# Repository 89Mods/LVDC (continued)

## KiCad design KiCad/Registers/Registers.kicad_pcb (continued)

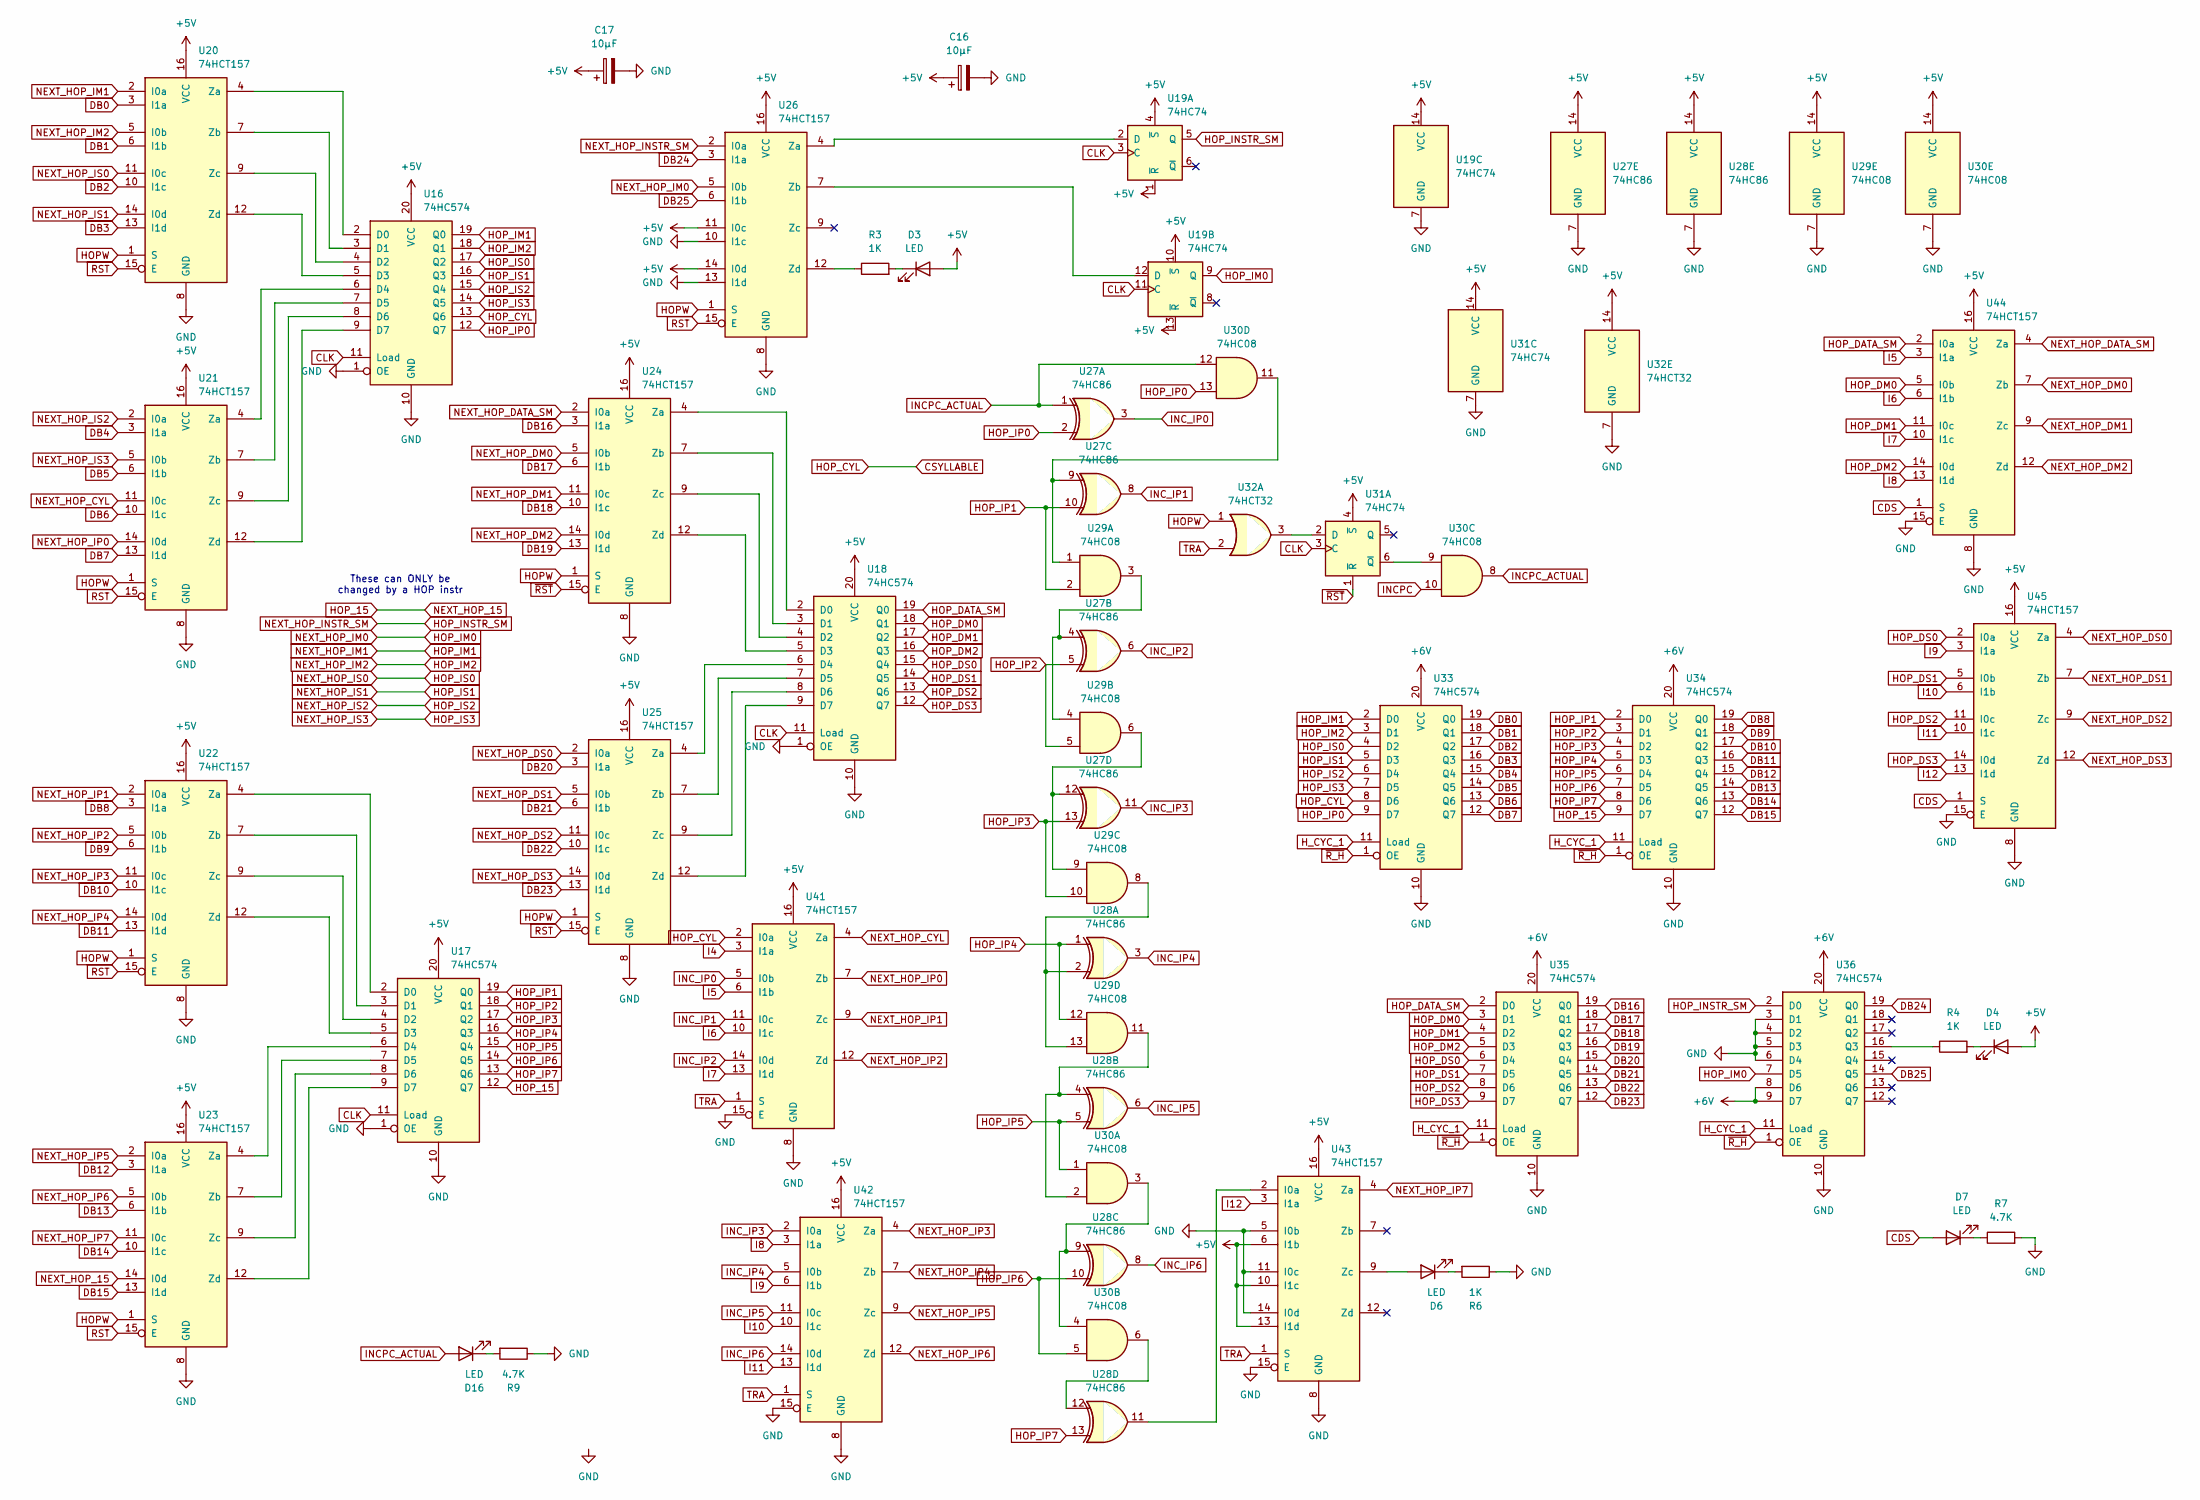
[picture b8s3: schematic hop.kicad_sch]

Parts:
C16, C17: 10µF; CP_Radial_D4.0mm_P2.00mm
D3, D4, D6, D7, D16: LED; LED_1206_3216Metric_Pad1.42x1.75mm_HandSolder
R3, R4, R6: 1K; R_1206_3216Metric_Pad1.30x1.75mm_HandSolder
R7, R9: 4.7K; R_1206_3216Metric_Pad1.30x1.75mm_HandSolder
U16, U17, U18, U33, U34, U35, U36: 74HC574; SO-20_12.8x7.5mm_P1.27mm
U19, U31: 74HC74; SO-14_3.9x8.65mm_P1.27mm
U20, U21, U22, U23, U24, U25, U26, U41, U42, U43, U44, U45: 74HCT157; SO-16_3.9x9.9mm_P1.27mm
U27, U28: 74HC86; SO-14_3.9x8.65mm_P1.27mm
U29, U30: 74HC08; SO-14_3.9x8.65mm_P1.27mm
U32: 74HCT32; SO-14_3.9x8.65mm_P1.27mm

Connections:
+5V: C16.1, C17.1, D3.2 (A), D4.2 (A), U16.20 (VCC), U17.20 (VCC), U18.20 (VCC), U19.1 (~R), U19.4 (~S), U19.10 (~S), U19.13 (~R), U19.14 (VCC), U20.16 (VCC), U21.16 (VCC), U22.16 (VCC), U23.16 (VCC), U24.16 (VCC), U25.16 (VCC), U26.11 (I0c), U26.14 (I0d), U26.16 (VCC), U27.14 (VCC), U28.14 (VCC), U29.14 (VCC), U30.14 (VCC), U31.4 (~S), U31.14 (VCC), U32.14 (VCC), U41.16 (VCC), U42.16 (VCC), U43.6 (I1b), U43.10 (I1c), U43.13 (I1d), U43.16 (VCC), U44.16 (VCC), U45.16 (VCC); also elsewhere on the board
+6V: U33.20 (VCC), U34.20 (VCC), U35.20 (VCC), U36.8 (D6), U36.9 (D7), U36.20 (VCC); also elsewhere on the board
CDS: D7.2 (A), U44.1 (S), U45.1 (S); also elsewhere on the board
CLK: U16.11 (Load), U17.11 (Load), U18.11 (Load), U19.3 (C), U19.11 (C), U31.3 (C); also elsewhere on the board
CSYLLABLE: U16.13 (Q6), U33.8 (D6), U41.2 (I0a); also elsewhere on the board
DB0: U20.3 (I1a), U33.19 (Q0); also elsewhere on the board
DB1: U20.6 (I1b), U33.18 (Q1); also elsewhere on the board
DB2: U20.10 (I1c), U33.17 (Q2); also elsewhere on the board
DB3: U20.13 (I1d), U33.16 (Q3); also elsewhere on the board
DB4: U21.3 (I1a), U33.15 (Q4); also elsewhere on the board
DB5: U21.6 (I1b), U33.14 (Q5); also elsewhere on the board
DB6: U21.10 (I1c), U33.13 (Q6); also elsewhere on the board
DB7: U21.13 (I1d), U33.12 (Q7); also elsewhere on the board
DB8: U22.3 (I1a), U34.19 (Q0); also elsewhere on the board
DB9: U22.6 (I1b), U34.18 (Q1); also elsewhere on the board
DB10: U22.10 (I1c), U34.17 (Q2); also elsewhere on the board
DB11: U22.13 (I1d), U34.16 (Q3); also elsewhere on the board
DB12: U23.3 (I1a), U34.15 (Q4); also elsewhere on the board
DB13: U23.6 (I1b), U34.14 (Q5); also elsewhere on the board
DB14: U23.10 (I1c), U34.13 (Q6); also elsewhere on the board
DB15: U23.13 (I1d), U34.12 (Q7); also elsewhere on the board
DB16: U24.3 (I1a), U35.19 (Q0); also elsewhere on the board
DB17: U24.6 (I1b), U35.18 (Q1); also elsewhere on the board
DB18: U24.10 (I1c), U35.17 (Q2); also elsewhere on the board
DB19: U24.13 (I1d), U35.16 (Q3); also elsewhere on the board
DB20: U25.3 (I1a), U35.15 (Q4); also elsewhere on the board
DB21: U25.6 (I1b), U35.14 (Q5); also elsewhere on the board
DB22: U25.10 (I1c), U35.13 (Q6); also elsewhere on the board
DB23: U25.13 (I1d), U35.12 (Q7); also elsewhere on the board
DB24: U26.3 (I1a), U36.19 (Q0); also elsewhere on the board
DB25: U26.6 (I1b), U36.14 (Q5); also elsewhere on the board
GND: C16.2, C17.2, R6.1, R7.2, R9.1, U16.1 (OE), U16.10 (GND), U17.1 (OE), U17.10 (GND), U18.1 (OE), U18.10 (GND), U19.7 (GND), U20.8 (GND), U21.8 (GND), U22.8 (GND), U23.8 (GND), U24.8 (GND), U25.8 (GND), U26.8 (GND), U26.10 (I1c), U26.13 (I1d), U27.7 (GND), U28.7 (GND), U29.7 (GND), U30.7 (GND), U31.7 (GND), U32.7 (GND), U33.10 (GND), U34.10 (GND), U35.10 (GND), U36.3 (D1), U36.4 (D2), U36.5 (D3), U36.6 (D4), U36.10 (GND), U41.8 (GND), U41.15 (E), U42.8 (GND), U42.15 (E), U43.5 (I0b), U43.8 (GND), U43.11 (I0c), U43.14 (I0d), U43.15 (E), U44.8 (GND), U44.15 (E), U45.8 (GND), U45.15 (E); also elsewhere on the board
HOPW: U20.1 (S), U21.1 (S), U22.1 (S), U23.1 (S), U24.1 (S), U25.1 (S), U26.1 (S), U32.1; also elsewhere on the board
HOP_15: U17.12 (Q7), U23.14 (I0d), U34.9 (D7); also elsewhere on the board
HOP_DATA_SM: U18.19 (Q0), U35.2 (D0), U44.2 (I0a)
HOP_DM0: U18.18 (Q1), U35.3 (D1), U44.5 (I0b); also elsewhere on the board
HOP_DM1: U18.17 (Q2), U35.4 (D2), U44.11 (I0c); also elsewhere on the board
HOP_DM2: U18.16 (Q3), U35.5 (D3), U44.14 (I0d); also elsewhere on the board
HOP_DS0: U18.15 (Q4), U35.6 (D4), U45.2 (I0a); also elsewhere on the board
HOP_DS1: U18.14 (Q5), U35.7 (D5), U45.5 (I0b); also elsewhere on the board
HOP_DS2: U18.13 (Q6), U35.8 (D6), U45.11 (I0c); also elsewhere on the board
HOP_DS3: U18.12 (Q7), U35.9 (D7), U45.14 (I0d); also elsewhere on the board
HOP_IM0: U19.9 (Q), U26.5 (I0b), U36.7 (D5); also elsewhere on the board
HOP_IM1: U16.19 (Q0), U20.2 (I0a), U33.2 (D0); also elsewhere on the board
HOP_IM2: U16.18 (Q1), U20.5 (I0b), U33.3 (D1); also elsewhere on the board
HOP_INSTR_SM: U19.5 (Q), U26.2 (I0a), U36.2 (D0)
HOP_IP0: U16.12 (Q7), U27.2, U30.13, U33.9 (D7); also elsewhere on the board
HOP_IP1: U17.19 (Q0), U27.10, U29.2, U34.2 (D0); also elsewhere on the board
HOP_IP2: U17.18 (Q1), U27.5, U29.5, U34.3 (D1); also elsewhere on the board
HOP_IP3: U17.17 (Q2), U27.13, U29.10, U34.4 (D2); also elsewhere on the board
HOP_IP4: U17.16 (Q3), U28.1, U29.12, U34.5 (D3); also elsewhere on the board
HOP_IP5: U17.15 (Q4), U28.5, U30.1, U34.6 (D4); also elsewhere on the board
HOP_IP6: U17.14 (Q5), U28.10, U30.5, U34.7 (D5); also elsewhere on the board
HOP_IP7: U17.13 (Q6), U28.13, U34.8 (D6); also elsewhere on the board
HOP_IS0: U16.17 (Q2), U20.11 (I0c), U33.4 (D2); also elsewhere on the board
HOP_IS1: U16.16 (Q3), U20.14 (I0d), U33.5 (D3); also elsewhere on the board
HOP_IS2: U16.15 (Q4), U21.2 (I0a), U33.6 (D4); also elsewhere on the board
HOP_IS3: U16.14 (Q5), U21.5 (I0b), U33.7 (D5); also elsewhere on the board
H_CYC_1: U33.11 (Load), U34.11 (Load), U35.11 (Load), U36.11 (Load); also elsewhere on the board
I4: U41.3 (I1a); also elsewhere on the board
I5: U41.6 (I1b), U44.3 (I1a); also elsewhere on the board
I6: U41.10 (I1c), U44.6 (I1b); also elsewhere on the board
I7: U41.13 (I1d), U44.10 (I1c); also elsewhere on the board
I8: U42.3 (I1a), U44.13 (I1d); also elsewhere on the board
I9: U42.6 (I1b), U45.3 (I1a); also elsewhere on the board
I10: U42.10 (I1c), U45.6 (I1b); also elsewhere on the board
I11: U42.13 (I1d), U45.10 (I1c); also elsewhere on the board
I12: U43.3 (I1a), U45.13 (I1d); also elsewhere on the board
INCPC: U30.10; also elsewhere on the board
INCPC_ACTUAL: D16.2 (A), U27.1, U30.8, U30.12
INC_IP0: U27.3, U41.5 (I0b)
INC_IP1: U27.8, U41.11 (I0c)
INC_IP2: U27.6, U41.14 (I0d)
INC_IP3: U27.11, U42.2 (I0a)
INC_IP4: U28.3, U42.5 (I0b)
INC_IP5: U28.6, U42.11 (I0c)
INC_IP6: U28.8, U42.14 (I0d)
NEXT_HOP_CYL: U21.11 (I0c), U41.4 (Za)
NEXT_HOP_DATA_SM: U24.2 (I0a), U44.4 (Za)
NEXT_HOP_DM0: U24.5 (I0b), U44.7 (Zb)
NEXT_HOP_DM1: U24.11 (I0c), U44.9 (Zc)
NEXT_HOP_DM2: U24.14 (I0d), U44.12 (Zd)
NEXT_HOP_DS0: U25.2 (I0a), U45.4 (Za)
NEXT_HOP_DS1: U25.5 (I0b), U45.7 (Zb)
NEXT_HOP_DS2: U25.11 (I0c), U45.9 (Zc)
NEXT_HOP_DS3: U25.14 (I0d), U45.12 (Zd)
NEXT_HOP_IP0: U21.14 (I0d), U41.7 (Zb)
NEXT_HOP_IP1: U22.2 (I0a), U41.9 (Zc)
NEXT_HOP_IP2: U22.5 (I0b), U41.12 (Zd)
NEXT_HOP_IP3: U22.11 (I0c), U42.4 (Za)
NEXT_HOP_IP4: U22.14 (I0d), U42.7 (Zb)
NEXT_HOP_IP5: U23.2 (I0a), U42.9 (Zc)
NEXT_HOP_IP6: U23.5 (I0b), U42.12 (Zd)
NEXT_HOP_IP7: U23.11 (I0c), U43.4 (Za)
unnamed: D3.1 (K), R3.2
unnamed: D4.1 (K), R4.2
unnamed: D6.2 (A), U43.9 (Zc)
unnamed: D6.1 (K), R6.2
unnamed: D7.1 (K), R7.1
unnamed: D16.1 (K), R9.2
unnamed: U16.2 (D0), U20.4 (Za)
unnamed: U16.3 (D1), U20.7 (Zb)
unnamed: U16.4 (D2), U20.9 (Zc)
unnamed: U16.5 (D3), U20.12 (Zd)
unnamed: U16.6 (D4), U21.4 (Za)
unnamed: U16.7 (D5), U21.7 (Zb)
unnamed: U16.8 (D6), U21.9 (Zc)
unnamed: U16.9 (D7), U21.12 (Zd)
unnamed: U17.2 (D0), U22.4 (Za)
unnamed: U17.3 (D1), U22.7 (Zb)
unnamed: U17.4 (D2), U22.9 (Zc)
unnamed: U17.5 (D3), U22.12 (Zd)
unnamed: U17.6 (D4), U23.4 (Za)
unnamed: U17.7 (D5), U23.7 (Zb)
unnamed: U17.8 (D6), U23.9 (Zc)
unnamed: U17.9 (D7), U23.12 (Zd)
unnamed: U18.2 (D0), U24.4 (Za)
unnamed: U18.3 (D1), U24.7 (Zb)
unnamed: U18.4 (D2), U24.9 (Zc)
unnamed: U18.5 (D3), U24.12 (Zd)
unnamed: U18.6 (D4), U25.4 (Za)
unnamed: U18.7 (D5), U25.7 (Zb)
unnamed: U18.8 (D6), U25.9 (Zc)
unnamed: U18.9 (D7), U25.12 (Zd)
unnamed: U19.2 (D), U26.4 (Za)
unnamed: U19.12 (D), U26.7 (Zb)
unnamed: R3.1, U26.12 (Zd)
unnamed: U27.4, U29.3, U29.4
unnamed: U27.9, U29.1, U30.11
unnamed: U27.12, U29.6, U29.9
unnamed: U28.2, U29.8, U29.13
unnamed: U28.4, U29.11, U30.2
unnamed: U28.9, U30.3, U30.4
unnamed: U28.12, U30.6
unnamed: U31.2 (D), U32.3
unnamed: U30.9, U31.6 (~Q)
unnamed: R4.1, U36.16 (Q3)
unnamed: U28.11, U43.2 (I0a)
RST: U20.15 (E), U21.15 (E), U22.15 (E), U23.15 (E), U25.15 (E), U26.15 (E); also elsewhere on the board
TRA: U32.2, U41.1 (S), U42.1 (S), U43.1 (S); also elsewhere on the board
~RST: U24.15 (E), U31.1 (~R); also elsewhere on the board
~R_H: U33.1 (OE), U34.1 (OE), U35.1 (OE), U36.1 (OE); also elsewhere on the board

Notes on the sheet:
These can ONLY be changed by a HOP instr

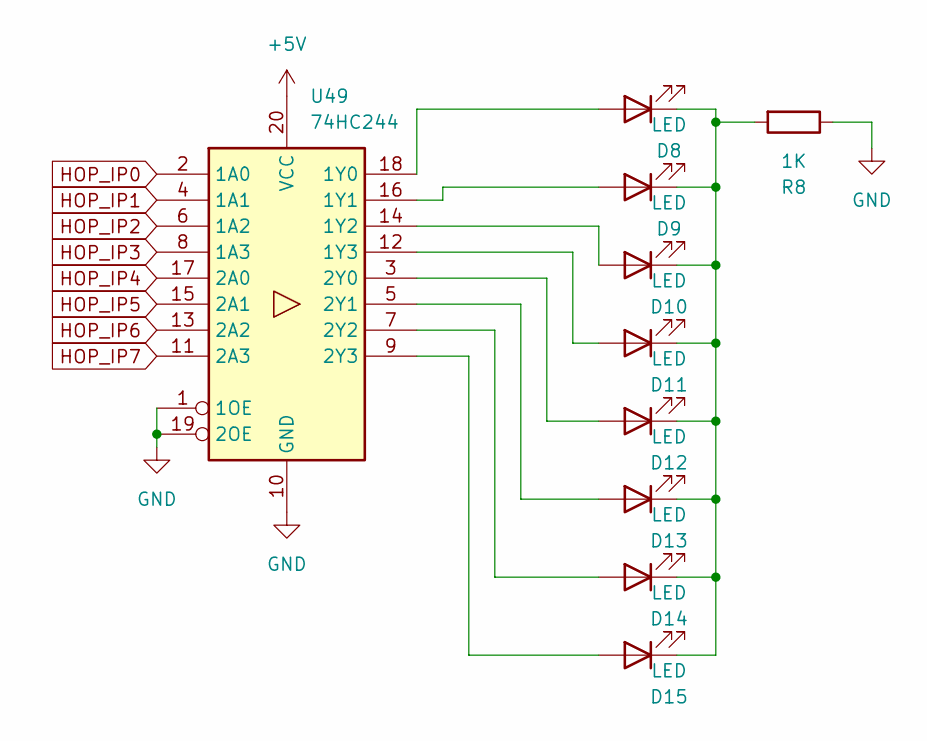
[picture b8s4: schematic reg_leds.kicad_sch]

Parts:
D8, D9, D10, D11, D12, D13, D14, D15: LED; LED_1206_3216Metric_Pad1.42x1.75mm_HandSolder
R8: 1K; R_1206_3216Metric_Pad1.30x1.75mm_HandSolder
U49: 74HC244; SO-20_12.8x7.5mm_P1.27mm

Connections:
+5V: U49.20 (VCC); also elsewhere on the board
GND: R8.1, U49.1 (1OE), U49.10 (GND), U49.19 (2OE); also elsewhere on the board
HOP_IP0: U49.2 (1A0); also elsewhere on the board
HOP_IP1: U49.4 (1A1); also elsewhere on the board
HOP_IP2: U49.6 (1A2); also elsewhere on the board
HOP_IP3: U49.8 (1A3); also elsewhere on the board
HOP_IP4: U49.17 (2A0); also elsewhere on the board
HOP_IP5: U49.15 (2A1); also elsewhere on the board
HOP_IP6: U49.13 (2A2); also elsewhere on the board
HOP_IP7: U49.11 (2A3); also elsewhere on the board
unnamed: D8.2 (A), U49.18 (1Y0)
unnamed: D9.2 (A), U49.16 (1Y1)
unnamed: D10.2 (A), U49.14 (1Y2)
unnamed: D8.1 (K), D9.1 (K), D10.1 (K), D11.1 (K), D12.1 (K), D13.1 (K), D14.1 (K), D15.1 (K), R8.2
unnamed: D11.2 (A), U49.12 (1Y3)
unnamed: D12.2 (A), U49.3 (2Y0)
unnamed: D13.2 (A), U49.5 (2Y1)
unnamed: D14.2 (A), U49.7 (2Y2)
unnamed: D15.2 (A), U49.9 (2Y3)

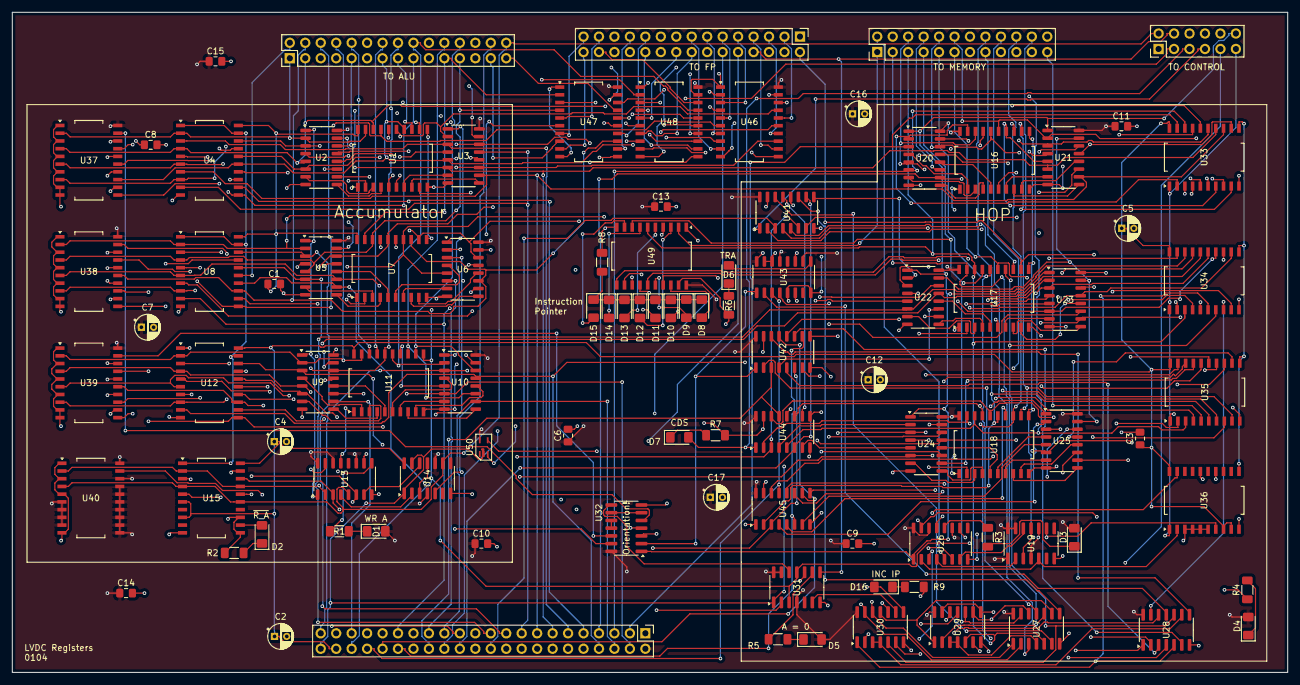
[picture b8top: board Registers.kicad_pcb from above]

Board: 4 copper layers, 209.5 x 108.5 mm, 97 parts (0 on the bottom side), 245 nets.

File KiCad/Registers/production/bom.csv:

Designator,Footprint,Quantity,Value,LCSC Part #
"C1, C10, C11, C13, C14, C15, C3, C6, C8, C9",0805,10,100nF,
"C12, C16, C17, C2, C4, C5, C7",CP_Radial_D4.0mm_P2.00mm,7,10µF,
"D1, D10, D11, D12, D13, D14, D15, D16, D2, D3, D4, D5, D6, D7, D8, D9",1206,16,LED,
J1,PinHeader_2x22_P2.54mm_Vertical,1,TO_BACKPLANE,
J2,PinHeader_2x15_P2.54mm_Vertical,1,ACCUMULATOR_OUT,
J3,PinHeader_2x06_P2.54mm_Vertical,1,FROM_CTRL,
J4,PinHeader_2x12_P2.54mm_Vertical,1,TO_MEMORY,
J5,PinHeader_2x15_P2.54mm_Vertical,1,TO_FP,
"R1, R2, R3, R4, R5, R6, R8",1206,7,1K,
"R7, R9",1206,2,4.7K,
"U1, U11, U16, U17, U18, U33, U34, U35, U36, U7",SO-20_12.8x7.5mm_P1.27mm,10,74HC574,
"U10, U13, U2, U20, U21, U22, U23, U24, U25, U26, U3, U41, U42, U43, U44, U45, U5, U6, U9",SO-16_3.9x9.9mm_P1.27mm,19,74HCT157,
"U12, U15, U4, U46, U47, U48, U49, U8",SO-20_12.8x7.5mm_P1.27mm,8,74HC244,
"U14, U19, U31",SO-14_3.9x8.65mm_P1.27mm,3,74HC74,
"U27, U28",SO-14_3.9x8.65mm_P1.27mm,2,74HC86,
"U29, U30",SO-14_3.9x8.65mm_P1.27mm,2,74HC08,
U32,SO-14_3.9x8.65mm_P1.27mm,1,74HCT32,
"U37, U38, U39, U40",SO-20_12.8x7.5mm_P1.27mm,4,74HC688,
U50,SOIC-6,1,74AHC1G04,

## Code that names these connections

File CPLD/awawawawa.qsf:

# -------------------------------------------------------------------------- #
#
# Copyright (C) 2025  Altera Corporation. All rights reserved.
# Your use of Altera Corporation's design tools, logic functions 
# and other software and tools, and any partner logic 
# functions, and any output files from any of the foregoing 
# (including device programming or simulation files), and any 
# associated documentation or information are expressly subject 
# to the terms and conditions of the Altera Program License 
# Subscription Agreement, the Altera Quartus Prime License Agreement,
# the Altera IP License Agreement, or other applicable license
# agreement, including, without limitation, that your use is for
# the sole purpose of programming logic devices manufactured by
# Altera and sold by Altera or its authorized distributors.  Please
# refer to the Altera Software License Subscription Agreements 
# on the Quartus Prime software download page.
#
# -------------------------------------------------------------------------- #
#
# Quartus Prime
# Version 24.1std.0 Build 1077 03/04/2025 SC Lite Edition
# Date created = 00:18:12  Mai 22, 2025
#
# -------------------------------------------------------------------------- #
#
# Notes:
#
# 1) The default values for assignments are stored in the file:
#		awawawawa_assignment_defaults.qdf
#    If this file doesn't exist, see file:
#		assignment_defaults.qdf
#
# 2) Intel recommends that you do not modify this file. This
#    file is updated automatically by the Quartus Prime software
#    and any changes you make may be lost or overwritten.
#
# -------------------------------------------------------------------------- #


set_global_assignment -name FAMILY "MAX II"
set_global_assignment -name DEVICE EPM240T100C5
set_global_assignment -name TOP_LEVEL_ENTITY awawawawa
set_global_assignment -name ORIGINAL_QUARTUS_VERSION 24.1STD.0
set_global_assignment -name PROJECT_CREATION_TIME_DATE "00:18:12  MAI 22, 2025"
set_global_assignment -name LAST_QUARTUS_VERSION "24.1std.0 Lite Edition"
set_global_assignment -name PROJECT_OUTPUT_DIRECTORY output_files
set_global_assignment -name MIN_CORE_JUNCTION_TEMP 0
set_global_assignment -name MAX_CORE_JUNCTION_TEMP 85
set_global_assignment -name DEVICE_FILTER_PACKAGE TQFP
set_global_assignment -name DEVICE_FILTER_PIN_COUNT 100
set_global_assignment -name ERROR_CHECK_FREQUENCY_DIVISOR "-1"
set_global_assignment -name POWER_EXT_SUPPLY_VOLTAGE_TO_REGULATOR 3.3V
set_global_assignment -name VERILOG_FILE awawawawa.v
set_location_assignment PIN_14 -to BDIR
set_location_assignment PIN_38 -to GPIO_LOAD
set_location_assignment PIN_39 -to GPIO_READb
set_location_assignment PIN_50 -to I[3]
set_location_assignment PIN_49 -to I[2]
set_location_assignment PIN_48 -to I[1]
set_location_assignment PIN_47 -to I[0]
set_location_assignment PIN_95 -to INTERRUPT
set_location_assignment PIN_40 -to INT_INHIBIT
set_location_assignment PIN_2 -to IORb
set_location_assignment PIN_3 -to IOWb
set_location_assignment PIN_37 -to KEY_CLEARb
set_location_assignment PIN_41 -to LED
set_location_assignment PIN_69 -to R1_SEGS[7]
set_location_assignment PIN_68 -to R1_SEGS[6]
set_location_assignment PIN_67 -to R1_SEGS[5]
set_location_assignment PIN_66 -to R1_SEGS[4]
set_location_assignment PIN_64 -to R1_SEGS[3]
set_location_assignment PIN_62 -to R1_SEGS[2]
set_location_assignment PIN_61 -to R1_SEGS[1]
set_location_assignment PIN_58 -to R1_SEGS[0]
set_location_assignment PIN_77 -to R2_SEGS[7]
set_location_assignment PIN_76 -to R2_SEGS[6]
set_location_assignment PIN_75 -to R2_SEGS[5]
set_location_assignment PIN_74 -to R2_SEGS[4]
set_location_assignment PIN_73 -to R2_SEGS[3]
set_location_assignment PIN_72 -to R2_SEGS[2]
set_location_assignment PIN_71 -to R2_SEGS[1]
set_location_assignment PIN_70 -to R2_SEGS[0]
set_location_assignment PIN_8 -to RCHECK
set_location_assignment PIN_6 -to RD0
set_location_assignment PIN_7 -to RD1
set_location_assignment PIN_57 -to RD0_OUT
set_location_assignment PIN_55 -to RD1_OUT
set_location_assignment PIN_5 -to RPULSE
set_location_assignment PIN_82 -to RPULSE_OUT
set_location_assignment PIN_100 -to SCK_FLASH
set_location_assignment PIN_97 -to SCK_LED1
set_location_assignment PIN_99 -to SDI
set_location_assignment PIN_98 -to SDO
set_location_assignment PIN_1 -to SID_CEb
set_location_assignment PIN_54 -to SSEL_R1[2]
set_location_assignment PIN_53 -to SSEL_R1[1]
set_location_assignment PIN_52 -to SSEL_R1[0]
set_location_assignment PIN_12 -to clk
set_location_assignment PIN_15 -to bus[15]
set_location_assignment PIN_16 -to bus[14]
set_location_assignment PIN_17 -to bus[13]
set_location_assignment PIN_18 -to bus[12]
set_location_assignment PIN_19 -to bus[11]
set_location_assignment PIN_20 -to bus[10]
set_location_assignment PIN_21 -to bus[9]
set_location_assignment PIN_26 -to bus[8]
set_location_assignment PIN_27 -to bus[7]
set_location_assignment PIN_28 -to bus[6]
set_location_assignment PIN_29 -to bus[5]
set_location_assignment PIN_30 -to bus[4]
set_location_assignment PIN_33 -to bus[3]
set_location_assignment PIN_34 -to bus[2]
set_location_assignment PIN_35 -to bus[1]
set_location_assignment PIN_36 -to bus[0]
set_global_assignment -name AUTO_RESTART_CONFIGURATION OFF
set_global_assignment -name ENABLE_OCT_DONE OFF
set_global_assignment -name ENABLE_CONFIGURATION_PINS OFF
set_global_assignment -name ENABLE_BOOT_SEL_PIN OFF
set_global_assignment -name USE_CONFIGURATION_DEVICE ON
set_global_assignment -name RESERVE_ALL_UNUSED_PINS "AS INPUT TRI-STATED WITH WEAK PULL-UP"
set_global_assignment -name ENABLE_DEVICE_WIDE_RESET ON
set_location_assignment PIN_86 -to BODGE0
set_location_assignment PIN_96 -to BODGE1
set_location_assignment PIN_83 -to TEMP
set_location_assignment PIN_91 -to SDA
set_location_assignment PIN_90 -to SCL

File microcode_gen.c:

#include <stdio.h>
#include <stdlib.h>
#include <string.h>
#include <stdint.h>

#define ALU_SWAPOPS (1 << 0)
#define ALU_OUTPUT (1 << 1)
#define ALU_IS_SHIFT (1 << 2)
#define ACCUM_WRITE (1 << 3)
#define ACCUM_OUTPUT (1 << 4)
#define INC_PC (1 << 5)
#define CDS_EXEC (1 << 6)
#define HOP_WRITE (1 << 7)
#define TRA_EXEC (1 << 8)
#define MEM_WR (1 << 9)
#define FETCH_CYC (1 << 10)
#define MEM_RD (1 << 11)
#define IS_EXM (1 << 12)
#define IS_IOEXEC (1 << 13)
#define MUL_RST ((1 << 14) | (1 << 15))
#define MUL_LDY_AND_START (1 << 15)
#define MUL_LDX_OR_LDZ (1 << 14)

#define STEP_0 0
#define STEP_1 1
#define STEP_2 2
#define STEP_3 3
#define STEP_4 4
#define STEP_5 5
#define STEP_6 6
#define STEP_7 7
#define A9 (1 << 7)
#define A8 (1 << 8)
#define ACCUM_ZERO (1 << 9)
#define ACCUM_NEG (1 << 10)

void wr_string(FILE *outfile, char *str) {
	while(1) {
		if(*str == 0) return;
		fwrite(str, 1, 1, outfile);
		str++;
	}
}

static uint16_t res[2048];

void instr_simple(uint8_t opcode, uint8_t step, uint16_t signals) {
	res[step + (opcode << 3)] = signals;
	res[step + (opcode << 3) + A9] = signals;
	res[step + (opcode << 3) + A8] = signals;
	res[step + (opcode << 3) + A8 + A9] = signals;
	res[step + (opcode << 3) + ACCUM_ZERO] = signals;
	res[step + (opcode << 3) + ACCUM_ZERO + A9] = signals;
	res[step + (opcode << 3) + ACCUM_ZERO + A8] = signals;
	res[step + (opcode << 3) + ACCUM_ZERO + A8 + A9] = signals;
	res[step + (opcode << 3) + ACCUM_NEG] = signals;
	res[step + (opcode << 3) + ACCUM_NEG + A9] = signals;
	res[step + (opcode << 3) + ACCUM_NEG + A8] = signals;
	res[step + (opcode << 3) + ACCUM_NEG + A8 + A9] = signals;
	res[step + (opcode << 3) + ACCUM_NEG + ACCUM_ZERO] = signals;
	res[step + (opcode << 3) + ACCUM_NEG + ACCUM_ZERO + A9] = signals;
	res[step + (opcode << 3) + ACCUM_NEG + ACCUM_ZERO + A8] = signals;
	res[step + (opcode << 3) + ACCUM_NEG + ACCUM_ZERO + A8 + A9] = signals;
}

void instr_pio(uint8_t opcode, uint8_t is_read, uint8_t step, uint16_t signals) {
	uint16_t o = is_read ? A9 : 0;
	res[step + (opcode << 3) + o] = signals;
	res[step + (opcode << 3) + A8 + o] = signals;
	res[step + (opcode << 3) + ACCUM_ZERO + o] = signals;
	res[step + (opcode << 3) + ACCUM_ZERO + A8 + o] = signals;
	res[step + (opcode << 3) + ACCUM_NEG + o] = signals;
	res[step + (opcode << 3) + ACCUM_NEG + A8 + o] = signals;
	res[step + (opcode << 3) + ACCUM_NEG + ACCUM_ZERO + A8 + o] = signals;
}

void instr_shift(uint8_t step, uint16_t signals) {
	res[step + (0xE << 3) + A9] = signals;
	res[step + (0xE << 3) + A9 + ACCUM_ZERO] = signals;
	res[step + (0xE << 3) + A9 + ACCUM_NEG] = signals;
	res[step + (0xE << 3) + A9 + ACCUM_ZERO + ACCUM_NEG] = signals;
}

void instr_cds(uint8_t step, uint16_t signals) {
	res[step + (0xE << 3) + A8] = signals;
	res[step + (0xE << 3) + A8 + ACCUM_ZERO] = signals;
	res[step + (0xE << 3) + A8 + ACCUM_NEG] = signals;
	res[step + (0xE << 3) + A8 + ACCUM_ZERO + ACCUM_NEG] = signals;
	res[step + (0xE << 3)] = signals;
	res[step + (0xE << 3) + ACCUM_ZERO] = signals;
	res[step + (0xE << 3) + ACCUM_NEG] = signals;
	res[step + (0xE << 3) + ACCUM_ZERO + ACCUM_NEG] = signals;
}

void instr_exm(uint8_t step, uint16_t signals) {
	res[step + (0xE << 3) + A8 + A9] = signals;
	res[step + (0xE << 3) + A8 + A9 + ACCUM_ZERO] = signals;
	res[step + (0xE << 3) + A8 + A9 + ACCUM_NEG] = signals;
	res[step + (0xE << 3) + A8 + A9 + ACCUM_ZERO + ACCUM_NEG] = signals;
}

int main(void) {
	memset(res, 0, 2048 * sizeof(uint16_t));
	
	for(uint8_t i = 0; i < 16; i++) {
		instr_simple(i, STEP_0, FETCH_CYC);
		instr_simple(i, STEP_1, INC_PC);
	}
	
	//HOP
	instr_simple(0x0, STEP_1, MEM_RD | HOP_WRITE);
	instr_simple(0x0, STEP_2, INC_PC);
	
	//SUB
	instr_simple(0x2, STEP_1, MEM_RD);
	instr_simple(0x2, STEP_2, ALU_OUTPUT | ACCUM_WRITE);
	instr_simple(0x2, STEP_3, INC_PC);
	
	//AND
	instr_simple(0x6, STEP_1, MEM_RD);
	instr_simple(0x6, STEP_2, ALU_OUTPUT | ACCUM_WRITE);
	instr_simple(0x6, STEP_3, INC_PC);
	
	//ADD
	instr_simple(0x7, STEP_1, MEM_RD);
	instr_simple(0x7, STEP_2, ALU_OUTPUT | ACCUM_WRITE);
	instr_simple(0x7, STEP_3, INC_PC);
	
	//XOR
	instr_simple(0x9, STEP_1, MEM_RD);
	instr_simple(0x9, STEP_2, ALU_OUTPUT | ACCUM_WRITE);
	instr_simple(0x9, STEP_3, INC_PC);
	
	//RSU
	instr_simple(0xD, STEP_1, MEM_RD | ALU_SWAPOPS);
	instr_simple(0xD, STEP_2, ALU_OUTPUT | ACCUM_WRITE | ALU_SWAPOPS);
	instr_simple(0xD, STEP_3, INC_PC | ALU_SWAPOPS);
	
	//CLA
	instr_simple(0xF, STEP_1, MEM_RD);
	instr_simple(0xF, STEP_2, ALU_OUTPUT | ACCUM_WRITE);
	instr_simple(0xF, STEP_3, INC_PC);
	
	//SHF
	instr_shift(STEP_1, ALU_IS_SHIFT);
	instr_shift(STEP_2, ALU_OUTPUT | ACCUM_WRITE);
	instr_shift(STEP_3, INC_PC);
	
	//CDS
	instr_cds(STEP_1, CDS_EXEC);
	instr_cds(STEP_2, INC_PC);
	
	//TRA
	instr_simple(0x8, STEP_1, TRA_EXEC);
	instr_simple(0x8, STEP_2, INC_PC);
	
	//TNZ
	instr_simple(0x4, STEP_1, TRA_EXEC);
	instr_simple(0x4, STEP_2, INC_PC);
	res[STEP_1 + (0x4 << 3) + ACCUM_ZERO] = 0;
	res[STEP_1 + (0x4 << 3) + ACCUM_ZERO + A9] = 0;
	res[STEP_1 + (0x4 << 3) + ACCUM_ZERO + A8] = 0;
	res[STEP_1 + (0x4 << 3) + ACCUM_ZERO + A8 + A9] = 0;
	res[STEP_1 + (0x4 << 3) + ACCUM_ZERO + ACCUM_NEG] = 0;
	res[STEP_1 + (0x4 << 3) + ACCUM_ZERO + ACCUM_NEG + A9] = 0;
	res[STEP_1 + (0x4 << 3) + ACCUM_ZERO + ACCUM_NEG + A8] = 0;
	res[STEP_1 + (0x4 << 3) + ACCUM_ZERO + ACCUM_NEG + A8 + A9] = 0;
	
	//TMI
	instr_simple(0xC, STEP_1, TRA_EXEC);
	instr_simple(0xC, STEP_2, INC_PC);
	res[STEP_1 + (0xC << 3) + ACCUM_ZERO] = 0;
	res[STEP_1 + (0xC << 3) + ACCUM_ZERO + A9] = 0;
	res[STEP_1 + (0xC << 3) + ACCUM_ZERO + A8] = 0;
	res[STEP_1 + (0xC << 3) + ACCUM_ZERO + A8 + A9] = 0;
	res[STEP_1 + (0xC << 3)] = 0;
	res[STEP_1 + (0xC << 3) + A9] = 0;
	res[STEP_1 + (0xC << 3) + A8] = 0;
	res[STEP_1 + (0xC << 3) + A8 + A9] = 0;
	
	//STO
	instr_simple(0xB, STEP_1, ACCUM_OUTPUT);
	instr_simple(0xB, STEP_2, ACCUM_OUTPUT | MEM_WR);
	instr_simple(0xB, STEP_3, INC_PC);
	
	//DIV
	instr_simple(0x3, STEP_1, 0);
	instr_simple(0x3, STEP_2, MUL_RST);
	instr_simple(0x3, STEP_3, ACCUM_OUTPUT | MUL_LDX_OR_LDZ);
	instr_simple(0x3, STEP_4, MEM_RD | MUL_LDY_AND_START);
	instr_simple(0x3, STEP_5, INC_PC);
	
	//MPY
	instr_simple(0x1, STEP_1, 0);
	instr_simple(0x1, STEP_2, MUL_RST);
	instr_simple(0x1, STEP_3, ACCUM_OUTPUT | MUL_LDX_OR_LDZ);
	instr_simple(0x1, STEP_4, MEM_RD | MUL_LDY_AND_START);
	instr_simple(0x1, STEP_5, INC_PC);
	
	//MPH
	instr_simple(0x5, STEP_1, 0);
	instr_simple(0x5, STEP_2, MUL_RST);
	instr_simple(0x5, STEP_3, ACCUM_OUTPUT | MUL_LDX_OR_LDZ);
	instr_simple(0x5, STEP_4, MEM_RD | MUL_LDY_AND_START);
	instr_simple(0x5, STEP_5, 0);
	instr_simple(0x5, STEP_6, MUL_RST | ACCUM_WRITE);
	instr_simple(0x5, STEP_7, INC_PC);
	
	//IS_EXM line
	for(int i = 0; i < 2048; i++) {
		if(((i >> 3) & 15) != 0xE) continue;
		if((i & A9) == 0) continue;
		if((i & A8) == 0) continue;
		res[i] |= IS_EXM;
	}
	
	//PIO
	instr_pio(0xA, 0, STEP_1, ACCUM_OUTPUT);
	instr_pio(0xA, 0, STEP_2, IS_IOEXEC | ACCUM_OUTPUT);
	instr_pio(0xA, 0, STEP_3, ACCUM_OUTPUT);
	instr_pio(0xA, 0, STEP_4, INC_PC);
	
	instr_pio(0xA, 1, STEP_1, IS_IOEXEC);
	instr_pio(0xA, 1, STEP_2, IS_IOEXEC | ACCUM_WRITE);
	instr_pio(0xA, 1, STEP_3, INC_PC);
	
	FILE *outfile = fopen("microcode.txt", "wb");
	if(!outfile) {
		printf("Failed to open output file\n");
		return 1;
	}
	char strbuff[128];
	wr_string(outfile, "v3.0 hex words addressed");
	for(int i = 0; i < 2048; i++) {
		if((i & 15) == 0) {
			sprintf(strbuff, "\n%03x:", i);
			wr_string(outfile, strbuff);
		}
		sprintf(strbuff, " %04x", res[i]);
		wr_string(outfile, strbuff);
	}
	wr_string(outfile, "\n");
	fclose(outfile);
	
	outfile = fopen("microcode_verilog_lo.txt", "wb");
	if(!outfile) {
		printf("Failed to open output file\n");
		return 1;
	}
	for(int i = 0; i < 2048; i++) {
		uint8_t val = res[i] & 0xFF;
		sprintf(strbuff, "%02x", val);
		wr_string(outfile, strbuff);
		if(((i + 1) & 15) == 0) wr_string(outfile, "\n");
		else wr_string(outfile, " ");
	}
	fclose(outfile);
	
	outfile = fopen("microcode_verilog_hi.txt", "wb");
	if(!outfile) {
		printf("Failed to open output file\n");
		return 1;
	}
	for(int i = 0; i < 2048; i++) {
		uint8_t val = res[i] >> 8;
		sprintf(strbuff, "%02x", val);
		wr_string(outfile, strbuff);
		if(((i + 1) & 15) == 0) wr_string(outfile, "\n");
		else wr_string(outfile, " ");
	}
	fclose(outfile);
	
	outfile = fopen("microcode_hi.dat", "wb");
	if(!outfile) {
		printf("Failed to open output file\n");
		return 1;
	}
	for(int i = 0; i < 2048; i++) {
		uint8_t val = res[i] >> 8;
		fwrite(&val, 1, 1, outfile);
	}
	fclose(outfile);
	
	outfile = fopen("microcode_lo.dat", "wb");
	if(!outfile) {
		printf("Failed to open output file\n");
		return 1;
	}
	for(int i = 0; i < 2048; i++) {
		uint8_t val = res[i] & 0xFF;
		fwrite(&val, 1, 1, outfile);
	}
	fclose(outfile);
	return 0;
}

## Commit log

2025-03-07 Initial
2025-03-12 Simple bootloader program.
2025-05-24 Prepare for bring-up
2025-08-15 Update schematics with fixes.
2025-08-19 Microcode fixes
2025-08-19 Fix R2 display CPLD bug
2025-08-19 Command handler done
2026-01-06 Main system software
